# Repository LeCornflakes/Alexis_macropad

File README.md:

# Macropalexis

Macropalexis is a 4 arrow key with a rotary encoder, an OLED Display. And uses QMK firmware

## Features:
- 128x32 OLED Display
- EC11 Rotary encoder to control the volume
- 4 Keys

## CAD Model:
Everything fits together using 4 M3 screws and heatset inserts.

It has 2 separate printed pieces. The base where the PCB sits, and the top cover.

## PCB
Here's my PCB! It was made in KiCad.

Schematic :

PCB :

## Firmware Overview
This hackpad uses [QMK](https://qmk.fm/) firmware for everything. 

- the rotary encoder changes volume. press to pause/play
- The 4 keys currently act as arrow key
- The OLED will display the volume and the music

## BOM:
Here should be everything you need to make this hackpad

- 4x Cherry MX Switches
- 4x DSA Keycaps
- 4x M3x5x4 Heatset inserts
- 4x M3x16mm screws
- 1x 0.91" 128x32 OLED Display
- 1x EC11 Rotary Encoder
- 1x XIAO RP2040

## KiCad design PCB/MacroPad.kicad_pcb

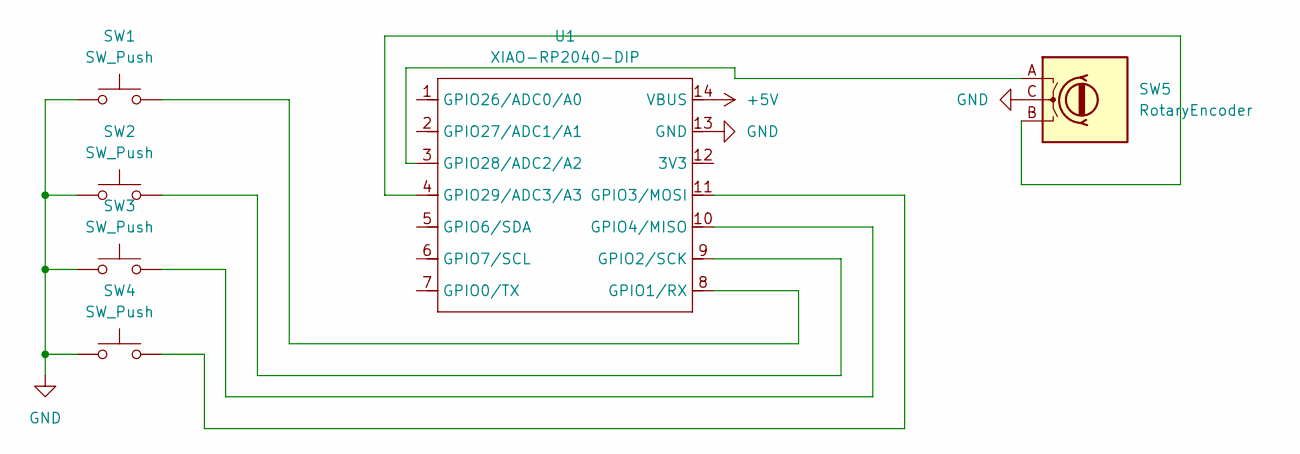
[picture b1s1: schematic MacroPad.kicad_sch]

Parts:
SW1, SW2, SW3, SW4: SW_Push; SW_Cherry_MX_1.00u_PCB
SW5: RotaryEncoder; RotaryEncoder_Alps_EC11E-Switch_Vertical_H20mm_CircularMoun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
U1: XIAO-RP2040-DIP

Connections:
+5V: U1.14 (VBUS)
GND: SW1.2, SW2.2, SW3.2, SW4.2, SW5.C, U1.13 (GND); also elsewhere on the board
unnamed: SW1.1, U1.8 (GPIO1/RX)
unnamed: SW2.1, U1.9 (GPIO2/SCK)
unnamed: SW4.1, U1.11 (GPIO3/MOSI)
unnamed: SW3.1, U1.10 (GPIO4/MISO)
unnamed: SW5.A, U1.3 (GPIO28/ADC2/A2)
unnamed: SW5.B, U1.4 (GPIO29/ADC3/A3)

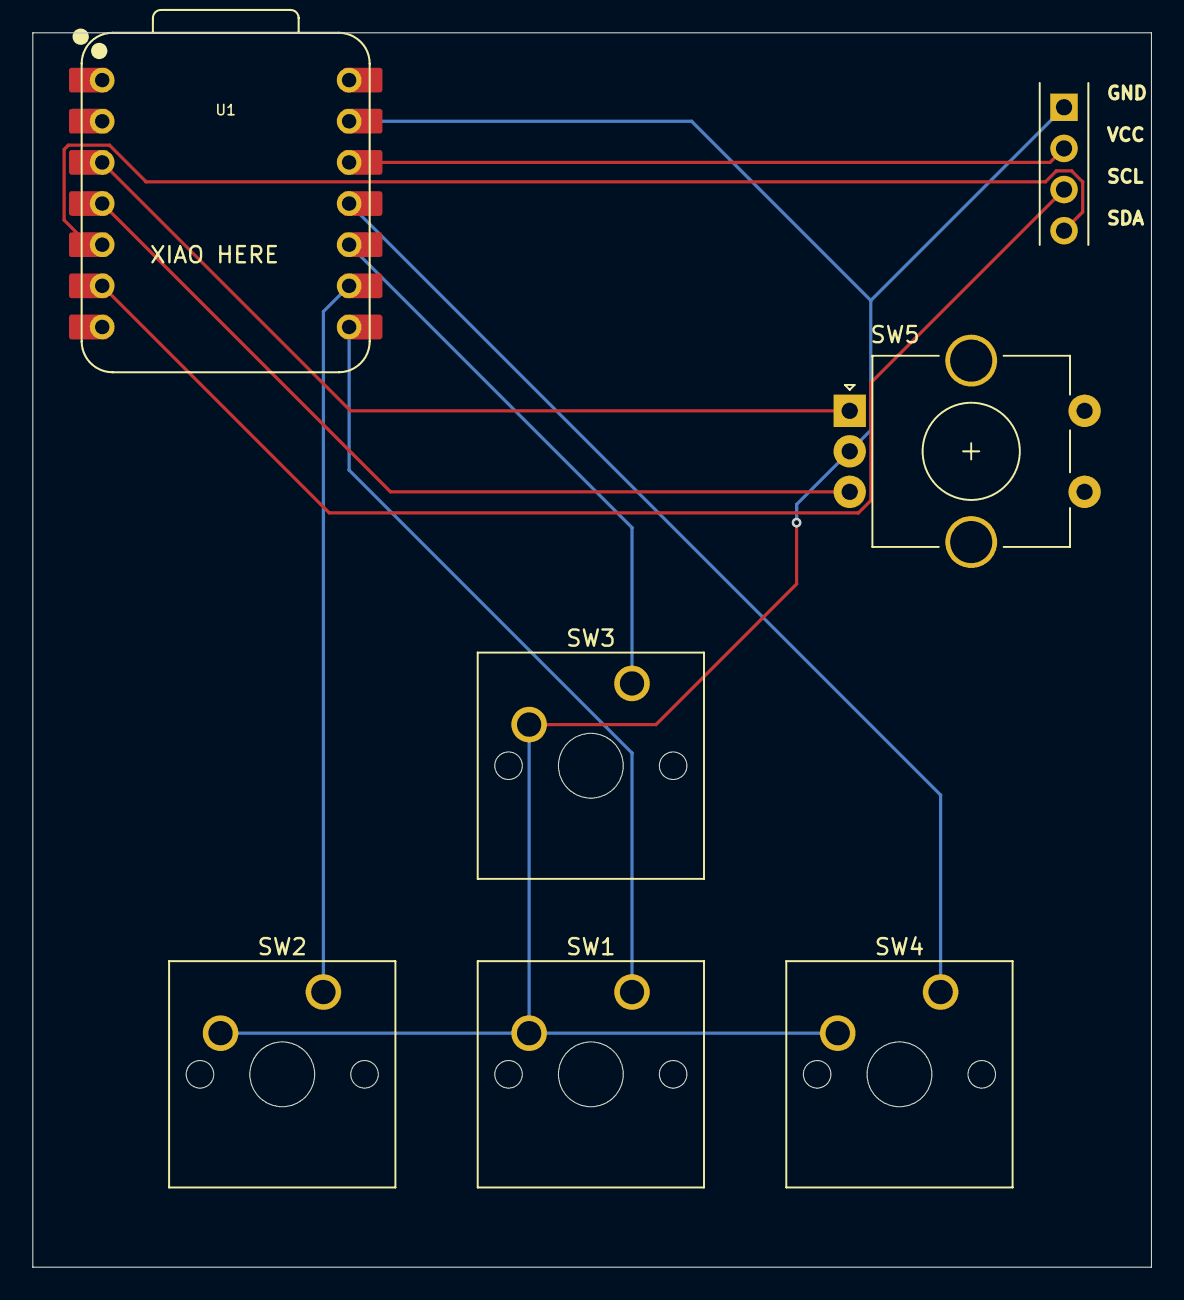
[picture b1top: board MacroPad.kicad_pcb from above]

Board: 2 copper layers, 69.1 x 76.2 mm, 7 parts (0 on the bottom side), 7 nets.

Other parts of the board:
J?: OLED_1x4; OLED_1x4_2.54mm

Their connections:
GND: J?.1; also elsewhere on the board

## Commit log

2026-01-11 All gbr file
2026-01-11 Pcb and shematic file
2026-01-12 STL file
2026-01-13 Create a README
2026-01-13 Folder for gbr files
2026-01-13 Folder for PCB
2026-01-13 Folder for STL
2026-01-13 Python file
2026-01-15 Revise README to document Orpheuspad features
    Expanded the README to include detailed features, specifications, and assembly instructions for the Orpheuspad macropad.
2026-01-15 Revise README for Macropalexis project
    Updated project name and descriptions in README.md. Adjusted features and BOM details.
2026-01-15 Assets folder
2026-01-15 Clarify printed pieces and firmware features in README
    Updated README to clarify printed pieces and firmware functionality.
2026-01-15 Rename Capture d'écran 2026-01-15 184433.png to Final_product_without_top.png
2026-01-15 Rename Capture d'écran 2026-01-15 184423.png to Final_product_with_top.png
2026-01-15 Replace schematic image with final product images
    Updated images in the README to show final product.
2026-01-15 Update the stl file
2026-01-15 Folder STEP
